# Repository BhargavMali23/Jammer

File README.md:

# Jammer
Bluetooth signal jammer using esp32 and nrf modules

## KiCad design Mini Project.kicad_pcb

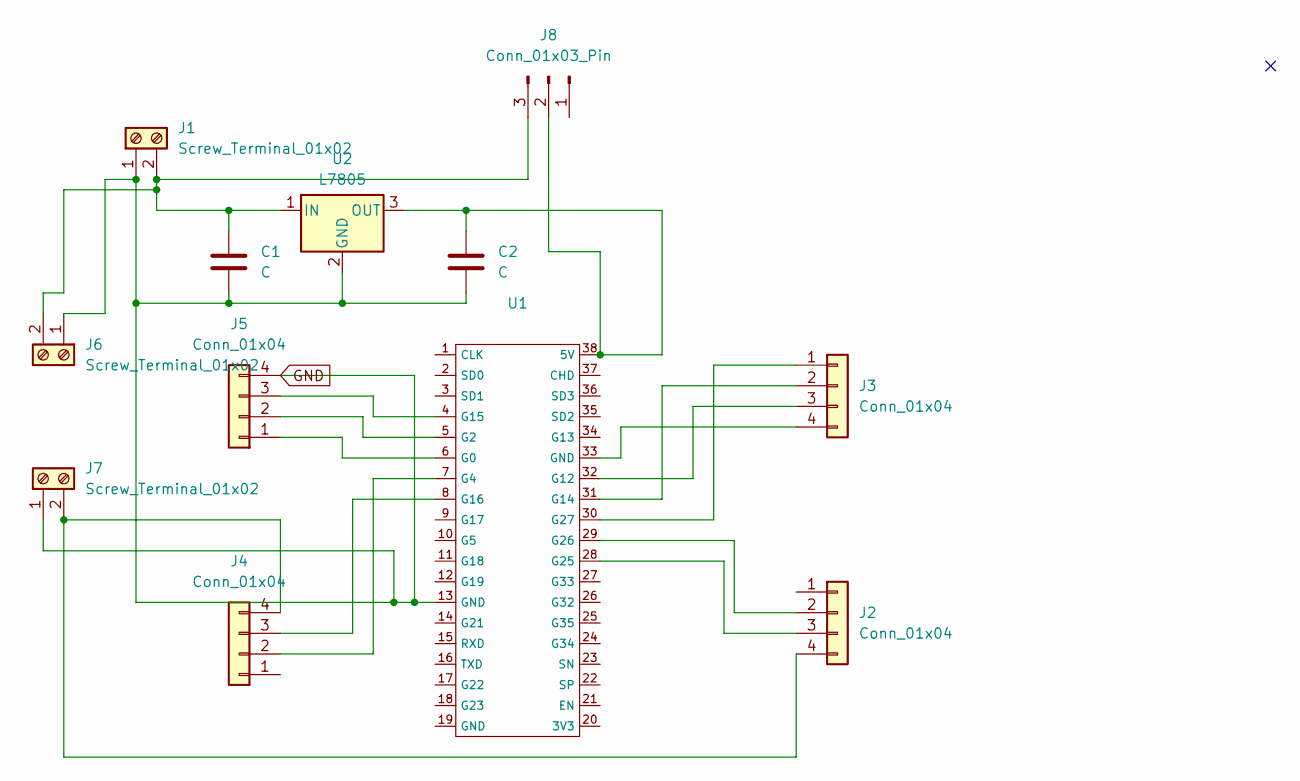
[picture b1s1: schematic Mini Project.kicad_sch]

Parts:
C1, C2: C; C_Axial_L3.8mm_D2.6mm_P7.50mm_Horizontal
J1, J6, J7: Screw_Terminal_01x02; TerminalBlock_RND_205-00276_1x02_P5.00mm_Vertical
J2, J3, J4, J5: Conn_01x04; PinHeader_1x04_P2.54mm_Vertical
J8: Conn_01x03_Pin; PinHeader_1x03_P2.54mm_Vertical
U1: Untitled
U2: L7805; TO-220-3_Vertical

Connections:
GND: C1.2, C2.2, J1.1, J5.4, J6.1, J7.1, U1.13 (GND), U2.2 (GND)
unnamed: C1.1, J1.2, J6.2, J8.3, U2.1 (IN)
unnamed: J2.2, U1.29 (G26)
unnamed: J2.3, U1.28 (G25)
unnamed: J2.4, J4.4, J7.2
unnamed: J3.1, U1.30 (G27)
unnamed: J3.2, U1.31 (G14)
unnamed: J3.3, U1.32 (G12)
unnamed: J3.4, U1.33 (GND)
unnamed: J4.2, U1.7 (G4)
unnamed: J4.3, U1.8 (G16)
unnamed: J5.1, U1.6 (G0)
unnamed: J5.2, U1.5 (G2)
unnamed: J5.3, U1.4 (G15)
unnamed: C2.1, J8.2, U1.38 (5V), U2.3 (OUT)

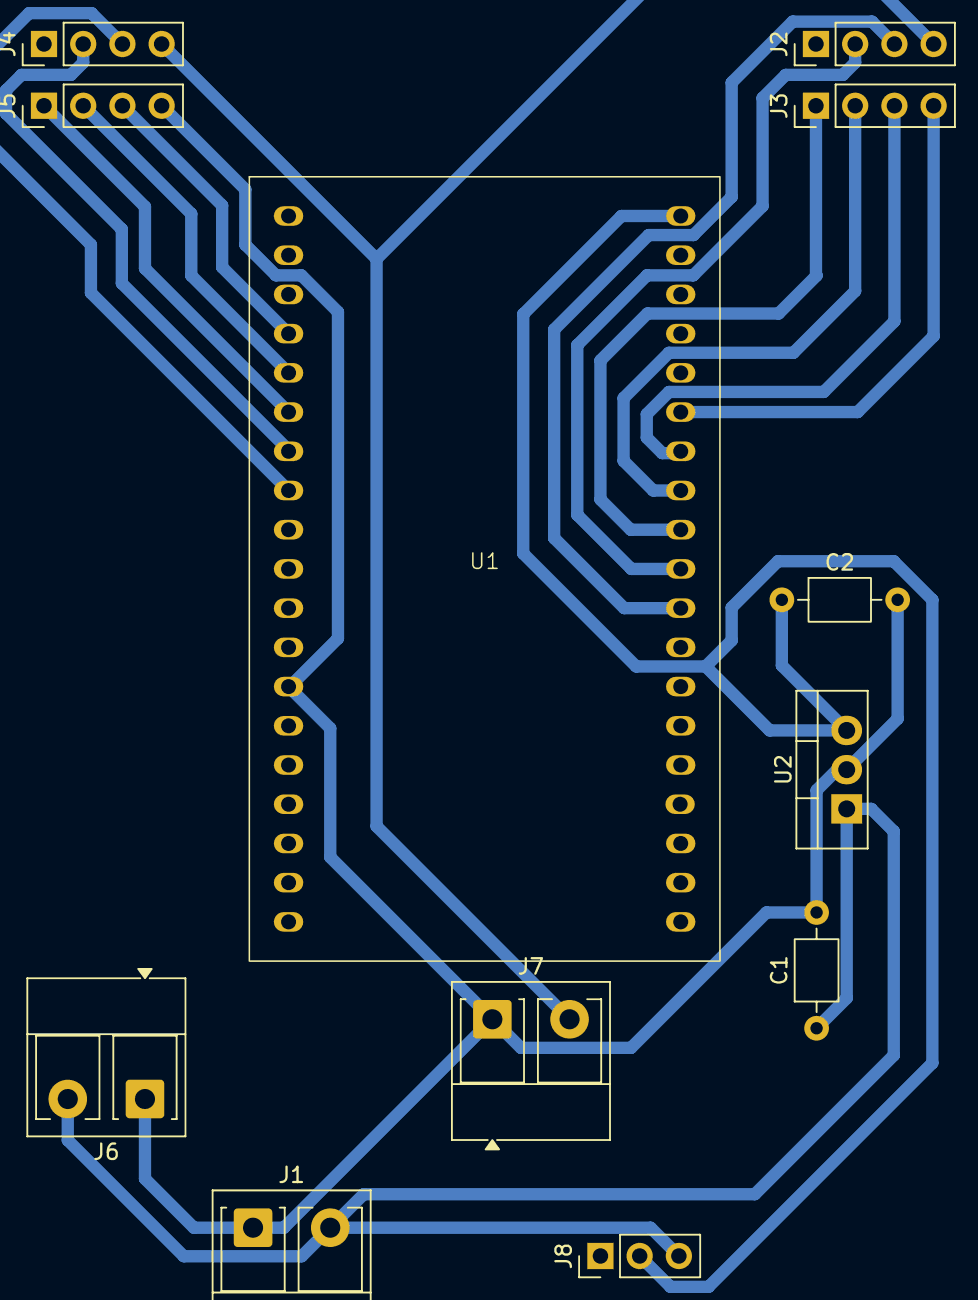
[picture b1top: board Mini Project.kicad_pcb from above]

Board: 2 copper layers, 12 parts (0 on the bottom side), 15 nets.
